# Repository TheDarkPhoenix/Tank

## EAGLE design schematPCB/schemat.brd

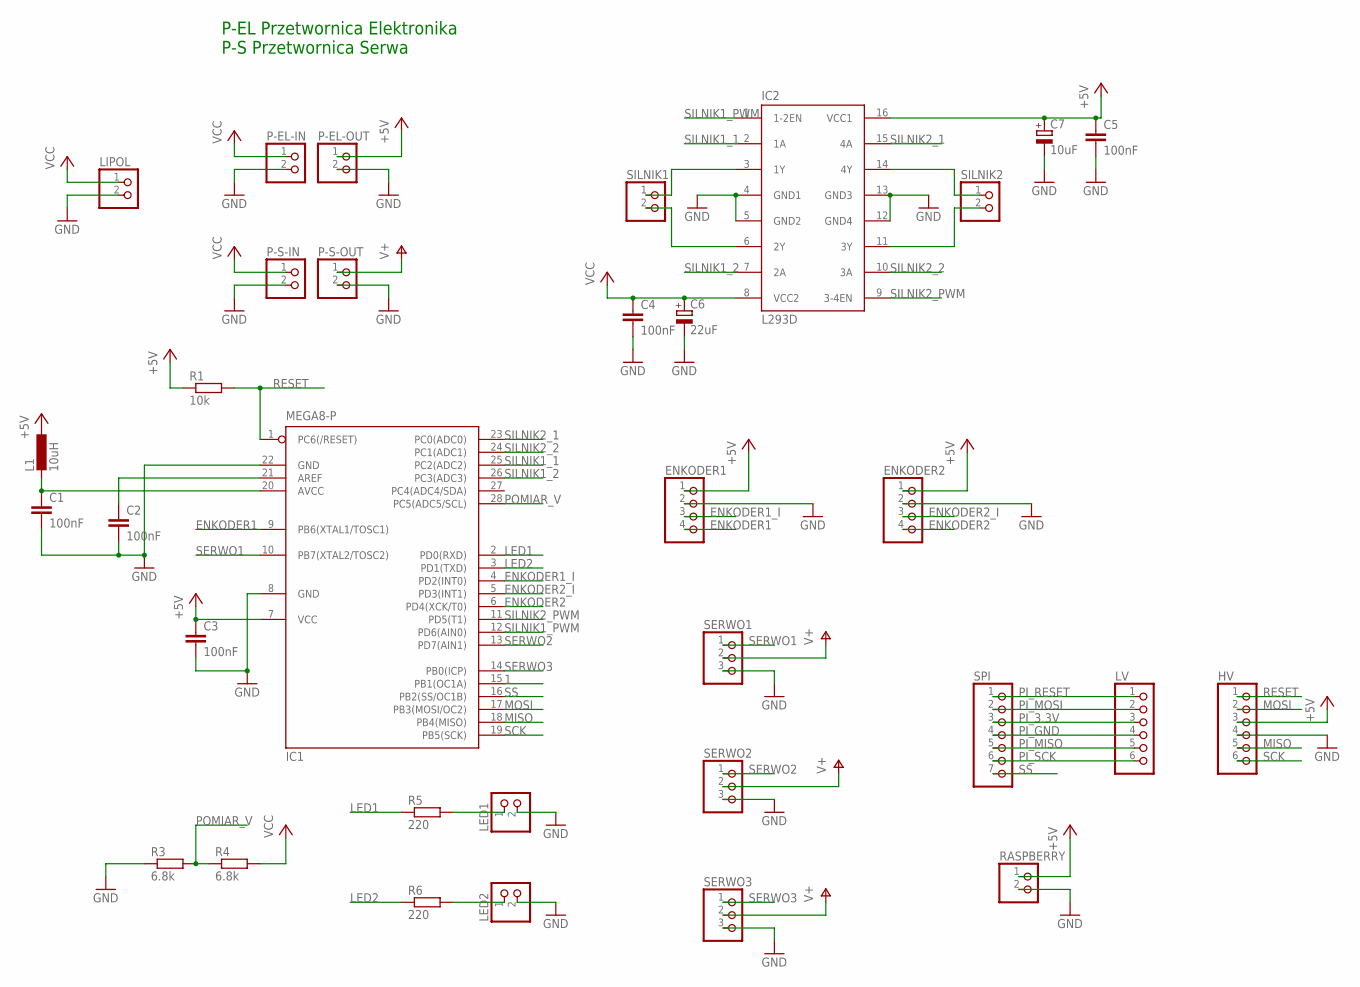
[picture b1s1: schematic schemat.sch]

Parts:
C1: 100nF; C050-030X075
C2, C3, C4, C5: 100nF; C025-030X050
C6: 22uF; E2,5-5
C7: 10uF; E2,5-5
ENKODER1, ENKODER2: PINHD-1X4; 1X04
HV: PINHD-1X6; 1X06
IC1: MEGA8-P; DIL28-3
IC2: L293D; DIL16
L1: 10uH; 0204/7
LED1, LED2: PINHD-1X2; 1X02
LIPOL: PINHD-1X2; 1X02
LV: PINHD-1X6; 1X06
P-EL-IN: PINHD-1X2; 1X02
P-EL-OUT: PINHD-1X2; 1X02
P-S-IN: PINHD-1X2; 1X02
P-S-OUT: PINHD-1X2; 1X02
R1: 10k; 0204/7
R3, R4: 6.8k; 0204/7
R5, R6: 220; 0204/7
RASPBERRY: PINHD-1X2; 1X02
SERWO1, SERWO2, SERWO3: PINHD-1X3; 1X03
SILNIK1, SILNIK2: PINHD-1X2; 1X02
SPI: PINHD-1X7; 1X07

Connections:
1: IC1.15 (PB1(OC1A))
+5V: C3.1, C5.1, C7.+, ENKODER1.1, ENKODER2.1, HV.3, IC1.7 (VCC), IC2.16 (VCC1), L1.1, P-EL-OUT.1, R1.1, RASPBERRY.1
ENKODER1: ENKODER1.4, IC1.9 (PB6(XTAL1/TOSC1))
ENKODER1_I: ENKODER1.3, IC1.4 (PD2(INT0))
ENKODER2: ENKODER2.4, IC1.6 (PD4(XCK/T0))
ENKODER2_I: ENKODER2.3, IC1.5 (PD3(INT1))
GND: C1.2, C2.2, C3.2, C4.2, C5.2, C6.-, C7.-, ENKODER1.2, ENKODER2.2, HV.4, IC1.8 (GND), IC1.22 (GND), IC2.4 (GND1), IC2.5 (GND2), IC2.12 (GND4), IC2.13 (GND3), LED1.2, LED2.2, LIPOL.2, P-EL-IN.2, P-EL-OUT.2, P-S-IN.2, P-S-OUT.2, R3.1, RASPBERRY.2, SERWO1.3, SERWO2.3, SERWO3.3
LED1: IC1.2 (PD0(RXD)), R5.1
LED2: IC1.3 (PD1(TXD)), R6.1
MISO: HV.5, IC1.18 (PB4(MISO))
MOSI: HV.2, IC1.17 (PB3(MOSI/OC2))
unnamed: IC2.14 (4Y), SILNIK2.1
unnamed: C2.1, IC1.21 (AREF)
unnamed: C1.1, IC1.20 (AVCC), L1.2
unnamed: IC2.11 (3Y), SILNIK2.2
unnamed: IC2.3 (1Y), SILNIK1.1
unnamed: LED1.1, R5.2
unnamed: LED2.1, R6.2
unnamed: IC2.6 (2Y), SILNIK1.2
PI_3.3V: LV.3, SPI.3
PI_GND: LV.4, SPI.4
PI_MISO: LV.5, SPI.5
PI_MOSI: LV.2, SPI.2
PI_RESET: LV.1, SPI.1
PI_SCK: LV.6, SPI.6
POMIAR_V: IC1.28 (PC5(ADC5/SCL)), R3.2, R4.1
RESET: HV.1, IC1.1 (PC6(/RESET)), R1.2
SCK: HV.6, IC1.19 (PB5(SCK))
SERWO1: IC1.10 (PB7(XTAL2/TOSC2)), SERWO1.1
SERWO2: IC1.13 (PD7(AIN1)), SERWO2.1
SERWO3: IC1.14 (PB0(ICP)), SERWO3.1
SILNIK1_1: IC1.25 (PC2(ADC2)), IC2.2 (1A)
SILNIK1_2: IC1.26 (PC3(ADC3)), IC2.7 (2A)
SILNIK1_PWM: IC1.12 (PD6(AIN0)), IC2.1 (1-2EN)
SILNIK2_1: IC1.23 (PC0(ADC0)), IC2.15 (4A)
SILNIK2_2: IC1.24 (PC1(ADC1)), IC2.10 (3A)
SILNIK2_PWM: IC1.11 (PD5(T1)), IC2.9 (3-4EN)
SS: IC1.16 (PB2(SS/OC1B)), SPI.7
V+: P-S-OUT.1, SERWO1.2, SERWO2.2, SERWO3.2
VCC: C4.1, C6.+, IC2.8 (VCC2), LIPOL.1, P-EL-IN.1, P-S-IN.1, R4.2

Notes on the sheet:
P-EL Przetwornica Elektronika P-S Przetwornica Serwa

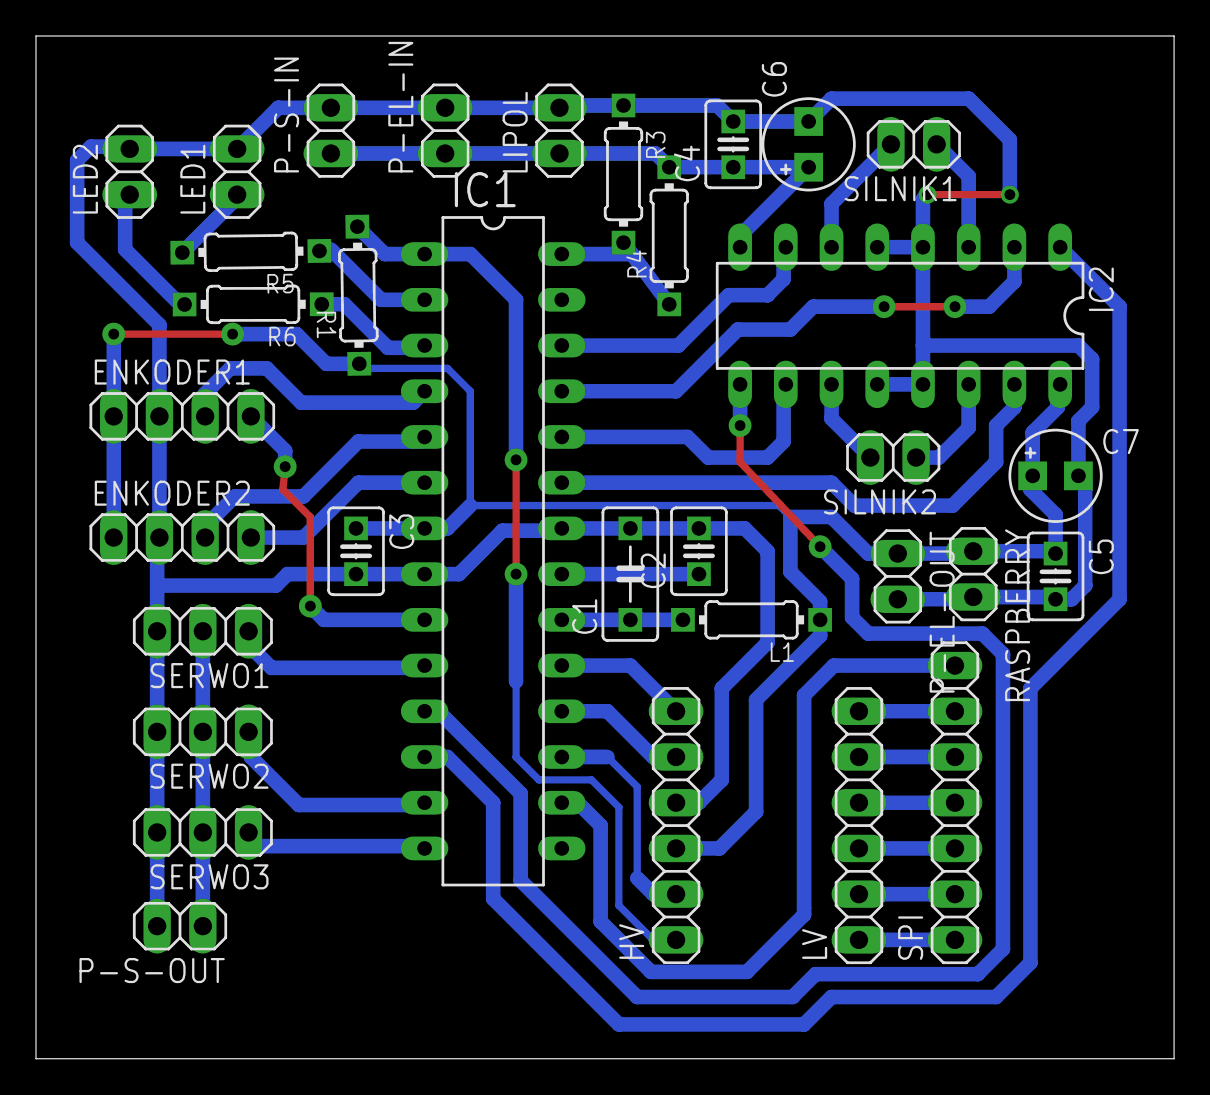
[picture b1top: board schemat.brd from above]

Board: 2 copper layers, 63.2 x 56.8 mm, 33 parts (0 on the bottom side), 39 nets.

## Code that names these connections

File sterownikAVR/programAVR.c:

#define F_CPU 1000000UL
#define NOOFSAMPLES 128

#include <avr/io.h>
#include <avr/interrupt.h>
#include <util/delay.h>

#define SILNIK1_1 _BV(PC2)
#define SILNIK1_2 _BV(PC3)
#define SILNIK1_PWM _BV(PD6)

#define SILNIK2_1 _BV(PC0)
#define SILNIK2_2 _BV(PC1)
#define SILNIK2_PWM _BV(PD5)


#define ENKODER1 _BV(PB6)
#define ENKODER1_INT _BV(PD2)

#define ENKODER2 _BV(PD4)
#define ENKODER2_INT _BV(PD3)


#define ADC1 _BV(PC5)


#define LED_URUCHOMIENIE _BV(PD0)
#define LED_ROZLADOWANIE _BV(PD1)


struct silnik
{
	uint8_t kierunek; // 1 - przod, 0 - tyl
	uint8_t v; // predkosc
};

struct silnik silnik1 = {1, 0};
struct silnik silnik2 = {1, 0};

struct enkoder
{
	int16_t val;
	uint8_t dir;
	uint8_t lastState;
	uint8_t part;
};

struct enkoder enk1 = {0,1,0,0};
struct enkoder enk2 = {0,1,0,0};

uint8_t ster = 0; // sterowanie programem
uint8_t a;
uint8_t w;

struct bateria
{
	uint16_t ADCval;
	uint8_t part;
};

struct bateria bateria1 = {0, 0};

void SPI_slave_init()
{
	DDRB |= _BV(PB4);
	SPCR = _BV(SPE) | _BV(SPIE);
	SPSR;
	SPDR;
}

void ADC_init()
{
	DDRC &= ~ADC1;
	PORTC &= ~ADC1;
	//MUX0|MUX2 - kanal ADC5
	ADMUX = _BV(REFS0) | _BV(MUX0) | _BV(MUX2);
	//napiecie odniesienia z avcc
	ADCSRA = _BV(ADEN) | _BV(ADIE) | _BV(ADATE) | _BV(ADSC) | _BV(ADPS0) | _BV(ADPS1) | _BV(ADPS2) ;
	// ADEN - ADC Enable | ADIE - ADC Interrupt Enable | ADPS - prescaler(w tym przypadku 128) | ADC Auto Trigger Enable | ADCS - ADC Start Conversion
}

void motor_init()
{
	DDRD |= SILNIK1_PWM | SILNIK2_PWM;
	TCCR0A = _BV(COM0A1) | _BV(COM0B1) | _BV(WGM00) | _BV(WGM01);
	TCCR0B = _BV(CS01) | _BV(CS00); // CS - clock source(ustawienie prescalera)
	OCR0A = 80;
	OCR0B = 80;
	
	DDRC |= SILNIK1_1 | SILNIK1_2 | SILNIK2_1 | SILNIK2_2;
	PORTC &= ~(SILNIK1_1 | SILNIK1_2 | SILNIK2_1 | SILNIK2_2);
}

void encoder_init()
{
	DDRD &= ~(ENKODER1_INT | ENKODER2_INT);
	PORTD |= ENKODER1_INT | ENKODER2_INT;

	DDRB &= ~(ENKODER1);
	PORTB |= ENKODER1;
	
	DDRD &= ~(ENKODER2);
	PORTD |= ENKODER2;

	EICRA |= _BV(ISC00) | _BV(ISC10);
	EIMSK |= _BV(INT0) | _BV(INT1);
}

ISR(ADC_vect)
{
	static uint32_t ADCaccum;
	static uint8_t sampleno;
	ADCaccum += ADC;
	sampleno++;
	if(sampleno==NOOFSAMPLES)
	{
		bateria1.ADCval = ADCaccum/NOOFSAMPLES;
		ADCaccum = 0;
		sampleno = 0;
		if(bateria1.ADCval < 690)
			PORTD |= LED_ROZLADOWANIE;
		else
			PORTD &= ~LED_ROZLADOWANIE;
		ADCSRA &= ~_BV(ADEN);
	}
}

ISR(INT0_vect)
{
	uint8_t Lstate = PIND & ENKODER1_INT;
	if((enk1.lastState == 0)&&(Lstate != 0))
	{
		uint8_t val = PINB & ENKODER1;
		if((val == 0)&&(enk1.dir == 1))
			enk1.dir = 0;
		else if((val != 0)&&(enk1.dir == 0))
			enk1.dir = 1;
	}

	enk1.lastState = Lstate;

	if(enk1.dir)
		enk1.val--;
	else
		enk1.val++;
}

ISR(INT1_vect)
{
	uint8_t Lstate = PIND & ENKODER2_INT;
	if((enk2.lastState == 0)&&(Lstate != 0))
	{
		uint8_t val = PIND & ENKODER2;
		if((val == 0)&&(enk2.dir == 1))
			enk2.dir = 0;
		else if((val != 0)&&(enk2.dir == 0))
			enk2.dir = 1;
	}

	enk2.lastState = Lstate;

	if(enk2.dir)
		enk2.val--;
	else
		enk2.val++;
}

ISR(SPI_STC_vect)
{
	a = SPDR;
	SPDR = 0;
	if(ster==0)
	{
		ster = a >> 1;
		if(ster == 1)
		{
			a <<= 7;
			a >>= 7;
			if(a)
				silnik1.kierunek = 1;
			else
				silnik1.kierunek = 0;
		}
		else if(ster == 2)
		{
			a <<= 7;
			a >>= 7;
			if(a)
				silnik2.kierunek = 1;
			else
				silnik2.kierunek = 0;
		}
	}
	else
	{
		if(ster == 1)
		{
			silnik1.v = a;
			if(silnik1.v == 0)
			{
				PORTC &= ~(SILNIK1_1 | SILNIK1_2);
			}
			else if(silnik1.kierunek)
			{
				PORTC |= SILNIK1_1;
				PORTC &= ~SILNIK1_2;
			}
			else
			{
				PORTC &= ~SILNIK1_1;
				PORTC |= SILNIK1_2;
			}
			OCR0A = a;
			ster = 0;
		}
		else if(ster == 2)
		{
			silnik2.v = a;
			if(silnik2.v == 0)
			{
				PORTC &= ~(SILNIK2_1 | SILNIK2_2);
			}
			else if(silnik2.kierunek)
			{
				PORTC |= SILNIK2_1;
				PORTC &= ~SILNIK2_2;
			}
			else
			{
				PORTC &= ~SILNIK2_1;
				PORTC |= SILNIK2_2;
			}
			OCR0B = a;
			ster = 0;
		}
	}
	
	if(ster==6)
	{
		if(enk1.part == 0)
		{		
			SPDR = enk1.val;
			enk1.part = 1;
		}
		else
		{
			SPDR = (enk1.val>>8);
			enk1.part = 0;
			enk1.val = 0;
			ster = 0;
		}
	}
	else if(ster==7)
	{
		if(enk2.part == 0)
		{		
			SPDR = enk2.val;
			enk2.part = 1;
		}
		else
		{
			SPDR = (enk2.val>>8);
			enk2.part = 0;
			enk2.val = 0;
			ster = 0;
		}
	}
	else if(ster==8)
	{
		if(bateria1.part == 0)
		{		
			SPDR = bateria1.ADCval;
			bateria1.part = 1;
		}
		else
		{
			SPDR = (bateria1.ADCval>>8);
			bateria1.part = 0;
			ster = 0;
		}
	}
	else if(ster == 9)
	{
		PORTD ^= LED_URUCHOMIENIE;
		ster = 0;
	}
	else if (ster!=1&&ster!=2)
		ster = 0;
}

int main()
{
	SPI_slave_init();
	motor_init();
	encoder_init();
	ADC_init();
	sei();
	DDRD |= LED_URUCHOMIENIE | LED_ROZLADOWANIE;
	PORTD &= ~LED_ROZLADOWANIE;
	PORTD |= LED_URUCHOMIENIE;
	while(1)
	{
		ADCSRA |= _BV(ADEN) | _BV(ADSC);
		_delay_ms(1000);
	}
}

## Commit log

2019-03-28 added license
2019-03-28 prawidlowe schematy
